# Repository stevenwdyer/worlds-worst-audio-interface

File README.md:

# World's Worst Audio Interface

This board consists of a TLV320AIC3100 audio codec, interfaced with a dual-core 480 MHz STM32H745IIT6 microcontroller, a 1/4" stereo jack with an op-amp buffer and inverting amplifier circuit, and a 1/8" headphone jack. It is USB-powered and uses SWD for flash and debug.

The goal of this project is to give me a custom, bare-metal platform on which I can try my hand at implementing audio effect algorithms from scratch, as well as record my own music.

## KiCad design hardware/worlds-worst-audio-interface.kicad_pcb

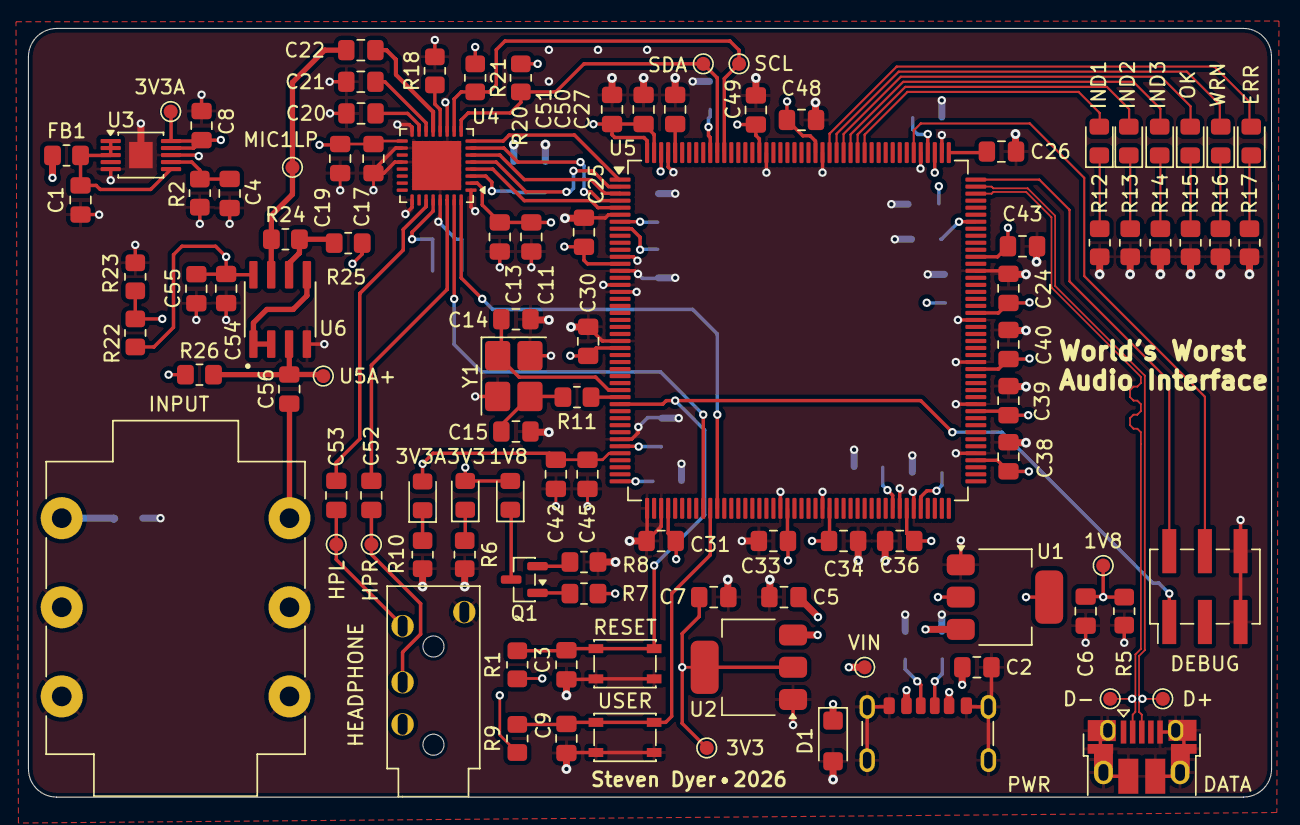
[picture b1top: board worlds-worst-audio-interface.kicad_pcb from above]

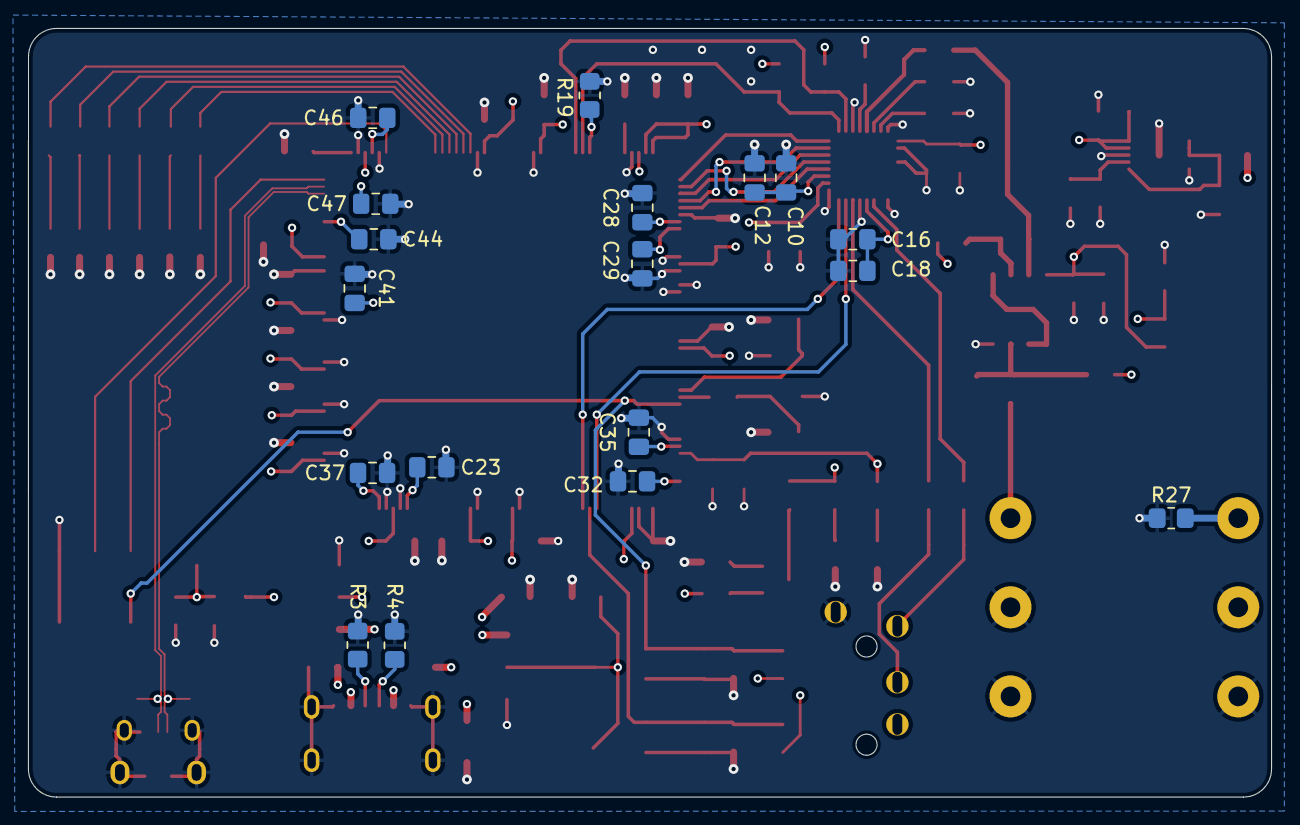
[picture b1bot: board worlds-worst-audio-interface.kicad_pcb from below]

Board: 4 copper layers, 88.6 x 54.8 mm, 121 parts (18 on the bottom side), 63 nets.

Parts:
1V8: +1V8; TestPoint_Pad_D1.0mm
1V8#2, 3V3A#2: LED; LED_0805_2012Metric_Pad1.15x1.40mm_HandSolder
3V3: 3V3_LED; LED_0805_2012Metric_Pad1.15x1.40mm_HandSolder
3V3#2: +3V3; TestPoint_Pad_D1.0mm
3V3A: +3.3VA; TestPoint_Pad_D1.0mm
C1, C8, C24: 4.7u; C_0805_2012Metric_Pad1.18x1.45mm_HandSolder
C2, C5, C10, C11, C16, C17, C55: 10u; C_0805_2012Metric_Pad1.18x1.45mm_HandSolder
C3, C9, C12, C13, C18, C19, C25, C28, C29, C30, C31, C33, C34, C35, C36, C37, C38, C39, C40, C41, C43, C44, C45, C46, C47, C48, C49, C50, C51, C54: 100n; C_0805_2012Metric_Pad1.18x1.45mm_HandSolder
C4: 470n; C_0805_2012Metric_Pad1.18x1.45mm_HandSolder
C6, C7: 22u; C_0805_2012Metric_Pad1.18x1.45mm_HandSolder
C14, C15: 22p; C_0805_2012Metric_Pad1.18x1.45mm_HandSolder
C20, C21, C22, C32, C42, C56: 1u; C_0805_2012Metric_Pad1.18x1.45mm_HandSolder
C23, C26, C27: 2.2u; C_0805_2012Metric_Pad1.18x1.45mm_HandSolder
C52, C53: 47u; C_0805_2012Metric_Pad1.18x1.45mm_HandSolder
D1: SMF5V0A; D_SMF
D+: USB_D+; TestPoint_Pad_D1.0mm
D-: USB_D-; TestPoint_Pad_D1.0mm
DATA: USB_B_Micro; USB_Micro-B_Amphenol_10103594-0001LF_Horizontal
DEBUG: Conn_02x03_Odd_Even; PinHeader_2x03_P2.54mm_Vertical_SMD
ERR: LED; LED_0805_2012Metric_Pad1.15x1.40mm_HandSolder
FB1: 1k@100MHz; R_0805_2012Metric_Pad1.20x1.40mm_HandSolder
HEADPHONE: PJ-320A
HPL: HPL; TestPoint_Pad_D1.0mm
HPR: HPR; TestPoint_Pad_D1.0mm
IND1, IND2, IND3: LED; LED_0805_2012Metric_Pad1.15x1.40mm_HandSolder
INPUT: NMJ6HCD2; Jack_6.35mm_Neutrik_NMJ6HCD2_Horizontal
MIC1LP: MIC1LP; TestPoint_Pad_D1.0mm
OK: LED; LED_0805_2012Metric_Pad1.15x1.40mm_HandSolder
PWR: USB_C_Receptacle_PowerOnly_6P; USB_C_Receptacle_GCT_USB4125-xx-x-0190_6P_TopMnt_Horizontal
Q1: ZXMN2A01F; SOT-23
R1, R9, R19, R22, R23, R25, R27: 10k; R_0805_2012Metric_Pad1.20x1.40mm_HandSolder
R2: 33.2k; R_0805_2012Metric_Pad1.20x1.40mm_HandSolder
R3, R4: 5k1; R_0805_2012Metric_Pad1.20x1.40mm_HandSolder
R5, R26: 1M; R_0805_2012Metric_Pad1.20x1.40mm_HandSolder
R6, R8, R10: 330; R_0805_2012Metric_Pad1.20x1.40mm_HandSolder
R7: 100; R_0805_2012Metric_Pad1.20x1.40mm_HandSolder
R11: 33; R_0805_2012Metric_Pad1.20x1.40mm_HandSolder
R12, R13, R14, R15, R16, R17: 680; R_0805_2012Metric_Pad1.20x1.40mm_HandSolder
R18: 2k2; R_0805_2012Metric_Pad1.20x1.40mm_HandSolder
R20, R21: 4k7; R_0805_2012Metric_Pad1.20x1.40mm_HandSolder
R24: 30k; R_0805_2012Metric_Pad1.20x1.40mm_HandSolder
RESET: SW_Push; SW_SPST_PTS810
SCL: I2C_SCL; TestPoint_Pad_D1.0mm
SDA: I2C_SDA; TestPoint_Pad_D1.0mm
U1: AMS1117-1.8; SOT-223-3_TabPin2
U2: AMS1117-3.3; SOT-223-3_TabPin2
U3: LT3042xMSE; MSOP-10-1EP_3x3mm_P0.5mm_EP1.68x1.88mm
U4: TLV320AIC3100; VQFN-32-1EP_5x5mm_P0.5mm_EP3.5x3.5mm
U5: STM32H745IITx; LQFP-176_24x24mm_P0.5mm
U5A+: U5A+; TestPoint_Pad_D1.0mm
U6: OPA2376xxD; OPA2376AID
USER: SW_Push; SW_SPST_PTS810
VIN: USB_VIN; TestPoint_Pad_D1.0mm
WRN: LED; LED_0805_2012Metric_Pad1.15x1.40mm_HandSolder
Y1: 12.288MHz; Crystal_SMD_3225-4Pin_3.2x2.5mm_HandSoldering

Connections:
+1V8: 1V8.1, C6.1, C10.1, C12.1, R5.1, R7.1, U1.2 (VO), U4.3 (DVDD)
+3.3VA: 3V3A.1, 3V3A#2.2 (A), C8.1, C17.1, C19.1, C42.1, C45.1, C54.1, C55.1, R22.1, U3.9 (OUTS), U3.10 (OUT), U4.17 (AVDD), U5.40 (VDDA), U6.8 (V+)
+3V3: 1V8#2.2 (A), 3V3.2 (A), 3V3#2.1, C7.1, C11.1, C13.1, C16.1, C18.1, C24.1, C25.1, C28.1, C29.1, C30.1, C31.1, C32.1, C33.1, C34.1, C35.1, C36.1, C37.1, C38.1, C39.1, C40.1, C41.1, C43.1, C44.1, C46.1, C47.1, C48.1, C49.1, C50.1, C51.1, R1.1, R9.1, R20.1, R21.1, U2.2 (VO), U4.2 (IOVDD), U4.28 (HPVDD), U5.7 (VDD), U5.8 (VBAT), U5.13 (VDD), U5.25 (VDD), U5.39 (VREF+), U5.44 (VDD), U5.48 (VDD), U5.65 (VDD), U5.71 (VDD), U5.82 (VDDLDO), U5.84 (VDD), U5.92 (VDD), U5.99 (VDD), U5.105 (VDD), U5.113 (VDD), U5.121 (VDD33_USB), U5.126 (VDD), U5.135 (VDDLDO), U5.136 (VDD), U5.152 (VDD), U5.160 (VDD), U5.174 (PDR_ON), U5.175 (VDDLDO), U5.176 (VDD)
/CODEC_GPIO: U4.32 (GPIO1), U5.55 (PB0)
/HPL: C53.1, U4.27 (HPL)
/HPR: C52.1, U4.30 (HPR)
/I2C_SCL: R21.2, SCL.1, U4.10 (SCL), U5.165 (PB6)
/I2C_SDA: R20.2, SDA.1, U4.9 (SDA), U5.166 (PB7)
/LED_ERR: ERR.2 (A), U5.150 (PD7)
/LED_IND1: IND1.2 (A), U5.145 (PD2)
/LED_IND2: IND2.2 (A), U5.146 (PD3)
/LED_IND3: IND3.2 (A), U5.147 (PD4)
/LED_OK: OK.2 (A), U5.148 (PD5)
/LED_WRN: U5.149 (PD6), WRN.2 (A)
/MIC1LP: C22.2, MIC1LP.1, R24.1, U6.7
/OSC_IN: C14.1, U5.31 (PH0), Y1.1
/OSC_OUT: R11.2, U5.32 (PH1)
/RESET: C3.1, DEBUG.1, R1.2, RESET.1, U5.33 (NRST)
/RESET_CODEC: U4.31 (~RESET), U5.53 (PC4)
/SAI1_FS_A: U4.6 (WCLK), U5.3 (PE4)
/SAI1_MCLK_A: U4.8 (MCLK), U5.1 (PE2)
/SAI1_SCK_A: U4.7 (BCLK), U5.4 (PE5)
/SAI1_SD_A: U4.4 (DOUT), U5.5 (PE6)
/SAI1_SD_B: U4.5 (DIN), U5.2 (PE3)
/SWDCLK: DEBUG.4, U5.138 (PA14)
/SWDIO: DEBUG.2, U5.132 (PA13)
/USB_D+: D+.1, DATA.3 (D+), U5.131 (PA12)
/USB_D-: D-.1, DATA.2 (D-), U5.130 (PA11)
/USB_VIN: C2.1, C5.1, D1.1 (A1), FB1.1, PWR.A9 (VBUS), PWR.B9 (VBUS), U1.3 (VI), U2.3 (VI), VIN.1
/USER_BTN: C9.1, R9.2, U5.54 (PC5), USER.1
/VBIAS: R22.2, R23.1, R25.2, R26.1
GND: C1.2, C2.2, C3.2, C4.2, C5.2, C6.2, C7.2, C8.2, C9.2, C10.2, C11.2, C12.2, C13.2, C14.2, C15.1, C16.2, C17.2, C18.2, C19.2, C20.2, C21.2, C23.2, C24.2, C25.2, C26.2, C27.2, C28.2, C29.2, C30.2, C31.2, C32.2, C33.2, C34.2, C35.2, C36.2, C37.2, C38.2, C39.2, C40.2, C41.2, C42.2, C43.2, C44.2, C45.2, C46.2, C47.2, C48.2, C49.2, C50.2, C51.2, C54.2, C55.2, D1.2 (A2), DATA.5 (GND), DATA.6 (Shield), DEBUG.5, DEBUG.6, HEADPHONE.1 (Sleeve), INPUT.R, INPUT.RN, INPUT.S, INPUT.SN, PWR.A12 (GND), PWR.B12 (GND), PWR.S1 (SHIELD), R2.2, R3.2, R4.2, R5.2, R6.1, R8.1, R10.1, R12.2, R13.2, R14.2, R15.2, R16.2, R17.2, R18.2, R19.2, R23.2, R27.1, RESET.2, U1.1 (GND), U2.1 (GND), U3.5 (ILIM), U3.8 (GND), U3.11 (GND), U4.1 (IOVSS), U4.11 (VOL/MICDET), U4.16 (AVSS), U4.18 (DVSS), U4.20 (SPKVSS), U4.25 (SPKVSS), U4.29 (HPVSS), U4.33 (EP), U5.6 (VSS), U5.12 (VSS), U5.14 (VSSSMPS), U5.16 (VDDSMPS), U5.17 (VFBSMPS), U5.24 (VSS), U5.38 (VSSA), U5.45 (VSS), U5.47 (VSS), U5.64 (VSS), U5.70 (VSS), U5.81 (VSS), U5.83 (VSS), U5.93 (VSS), U5.100 (VSS), U5.106 (VSS), U5.112 (VSS), U5.119 (VSS), U5.134 (VSS), U5.137 (VSS), U5.151 (VSS), U5.159 (VSS), U5.173 (VSS), U6.4 (V-), USER.2, Y1.2 (G), Y1.4 (G)
unnamed: C15.2, R11.1, Y1.3
unnamed: C23.1, U5.80 (VCAP)
unnamed: C26.1, U5.133 (VCAP)
unnamed: C27.1, U5.172 (VCAP)
unnamed: C56.2, INPUT.T
unnamed: 3V3.1 (K), R6.2
unnamed: 1V8#2.1 (K), Q1.3 (D)
unnamed: 3V3A#2.1 (K), R10.2
unnamed: IND1.1 (K), R12.1
unnamed: IND2.1 (K), R13.1
unnamed: IND3.1 (K), R14.1
unnamed: OK.1 (K), R15.1
unnamed: R16.1, WRN.1 (K)
unnamed: ERR.1 (K), R17.1
unnamed: PWR.A5 (CC1), R4.1
unnamed: PWR.B5 (CC2), R3.1
unnamed: INPUT.TN, R27.2
unnamed: Q1.1 (G), R7.2
unnamed: Q1.2 (S), R8.2
unnamed: C1.1, FB1.2, U3.1 (IN), U3.2 (IN), U3.3 (EN/UV), U3.6 (PGFB)
unnamed: C4.1, R2.1, U3.7 (SET)
unnamed: C20.1, U4.15 (MIC1LM)
unnamed: C22.1, U4.13 (MIC1LP)
unnamed: C21.1, U4.14 (MIC1RP)
unnamed: R18.1, U4.12 (MICBIAS)
unnamed: R19.1, U5.167 (BOOT0)
unnamed: C56.1, R26.2, U5A+.1, U6.3 (+)
unnamed: U6.1, U6.2 (-), U6.5 (+)
unnamed: R24.2, R25.1, U6.6 (-)
unnamed: C52.2, HEADPHONE.3 (Ring1), HPR.1
unnamed: C53.2, HEADPHONE.2 (Tip), HPL.1

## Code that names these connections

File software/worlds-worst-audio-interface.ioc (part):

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Mcu.Name=STM32H745IITx
Mcu.Package=LQFP176
Mcu.UserName=STM32H745IITx
PA11.GPIOParameters=PinAttribute
PA11.Mode=Device_Only
PA11.PinAttribute=CortexM4
PA11.Signal=USB_OTG_FS_DM
PA12.GPIOParameters=PinAttribute
PA12.Mode=Device_Only
PA12.PinAttribute=CortexM4
PA12.Signal=USB_OTG_FS_DP
PA13\ (JTMS/SWDIO).GPIOParameters=PinAttribute
PA13\ (JTMS/SWDIO).Mode=Serial_Wire
PA13\ (JTMS/SWDIO).PinAttribute=CortexM7
PA13\ (JTMS/SWDIO).Signal=DEBUG_JTMS-SWDIO
PA14\ (JTCK/SWCLK).GPIOParameters=PinAttribute
PA14\ (JTCK/SWCLK).Mode=Serial_Wire
PA14\ (JTCK/SWCLK).PinAttribute=CortexM7
PA14\ (JTCK/SWCLK).Signal=DEBUG_JTCK-SWCLK
PB6.GPIOParameters=PinAttribute
PB6.Mode=I2C
PB6.PinAttribute=CortexM7
PB6.Signal=I2C1_SCL
PB7.GPIOParameters=PinAttribute
PB7.Mode=I2C
PB7.PinAttribute=CortexM7
PB7.Signal=I2C1_SDA
PD2.GPIOParameters=GPIO_Label,PinAttribute
PD2.GPIO_Label=LED_IND1
PD2.PinAttribute=Free
PD2.Signal=GPIO_Output
PD3.GPIOParameters=GPIO_Label,PinAttribute
PD3.GPIO_Label=LED_IND2
PD3.PinAttribute=Free
PD3.Signal=GPIO_Output
PD4.GPIOParameters=GPIO_Label,PinAttribute
PD4.GPIO_Label=LED_IND3
PD4.PinAttribute=Free
PD4.Signal=GPIO_Output
PD5.GPIOParameters=GPIO_Label,PinAttribute
PD5.GPIO_Label=LED_OK
PD5.PinAttribute=Free
PD5.Signal=GPIO_Output
PD6.GPIOParameters=GPIO_Label,PinAttribute
PD6.GPIO_Label=LED_WRN
PD6.PinAttribute=Free
PD6.Signal=GPIO_Output
PD7.GPIOParameters=GPIO_Label,PinAttribute
PD7.GPIO_Label=LED_ERR
PD7.PinAttribute=Free
PD7.Signal=GPIO_Output
PE2.GPIOParameters=PinAttribute
PE2.Mode=SAI_A_MasterWithClock
PE2.PinAttribute=CortexM7
PE2.Signal=SAI1_MCLK_A
PE3.GPIOParameters=PinAttribute
PE3.Mode=SAI_B_SyncSlave
PE3.PinAttribute=CortexM7
PE3.Signal=SAI1_SD_B
PE4.GPIOParameters=PinAttribute
PE4.Mode=SAI_A_MasterWithClock
PE4.PinAttribute=CortexM7
PE4.Signal=SAI1_FS_A
PE5.GPIOParameters=PinAttribute
PE5.Mode=SAI_A_MasterWithClock
PE5.PinAttribute=CortexM7
PE5.Signal=SAI1_SCK_A
PE6.GPIOParameters=PinAttribute
PE6.Mode=SAI_A_MasterWithClock
PE6.PinAttribute=CortexM7
PE6.Signal=SAI1_SD_A
PH0-OSC_IN\ (PH0).GPIOParameters=PinAttribute
PH0-OSC_IN\ (PH0).Mode=HSE-External-Oscillator
PH0-OSC_IN\ (PH0).PinAttribute=Free
PH0-OSC_IN\ (PH0).Signal=RCC_OSC_IN
PH1-OSC_OUT\ (PH1).GPIOParameters=PinAttribute
PH1-OSC_OUT\ (PH1).Mode=HSE-External-Oscillator
PH1-OSC_OUT\ (PH1).PinAttribute=Free
PH1-OSC_OUT\ (PH1).Signal=RCC_OSC_OUT
RCC.SYSCLKFreq_VALUE=64000000
board=custom
